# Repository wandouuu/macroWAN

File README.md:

# vWAN-micropad
PCB design for personal macropad!

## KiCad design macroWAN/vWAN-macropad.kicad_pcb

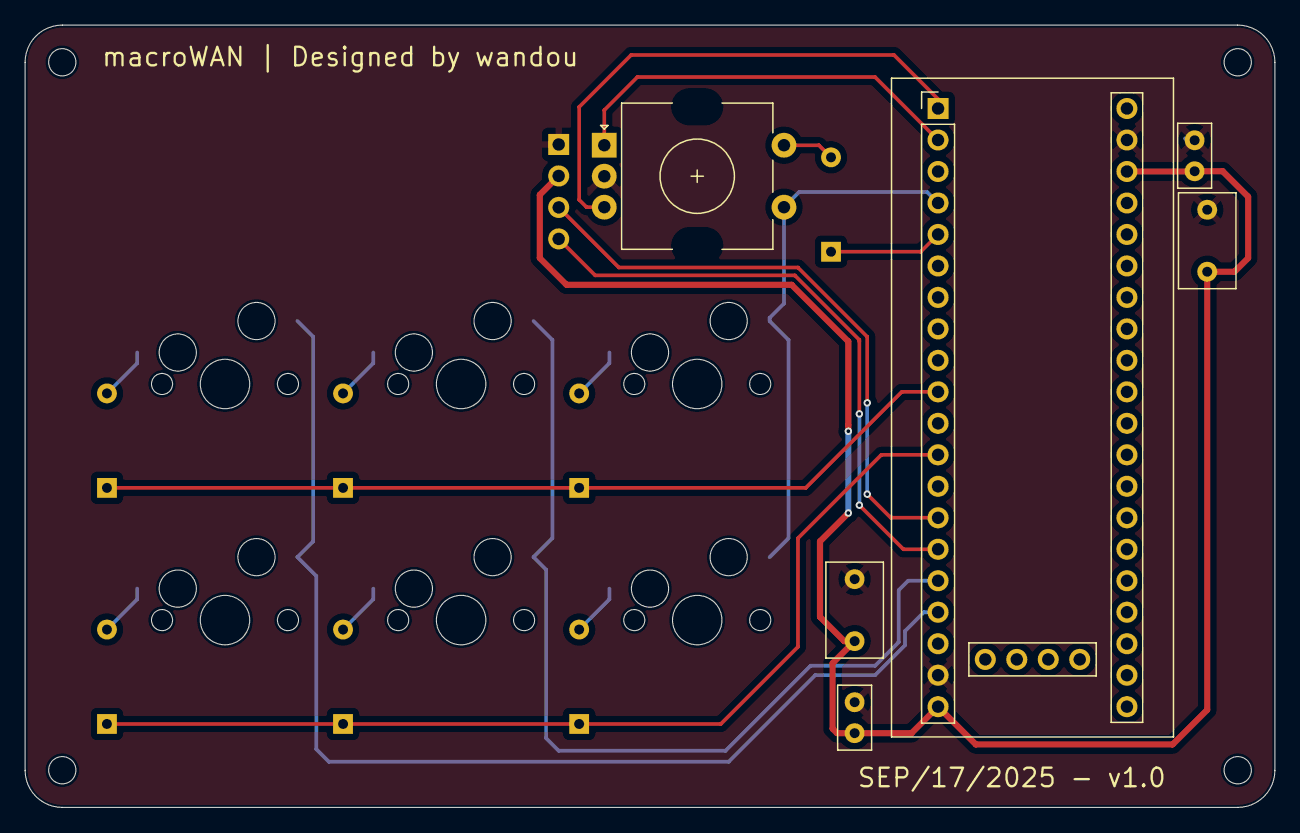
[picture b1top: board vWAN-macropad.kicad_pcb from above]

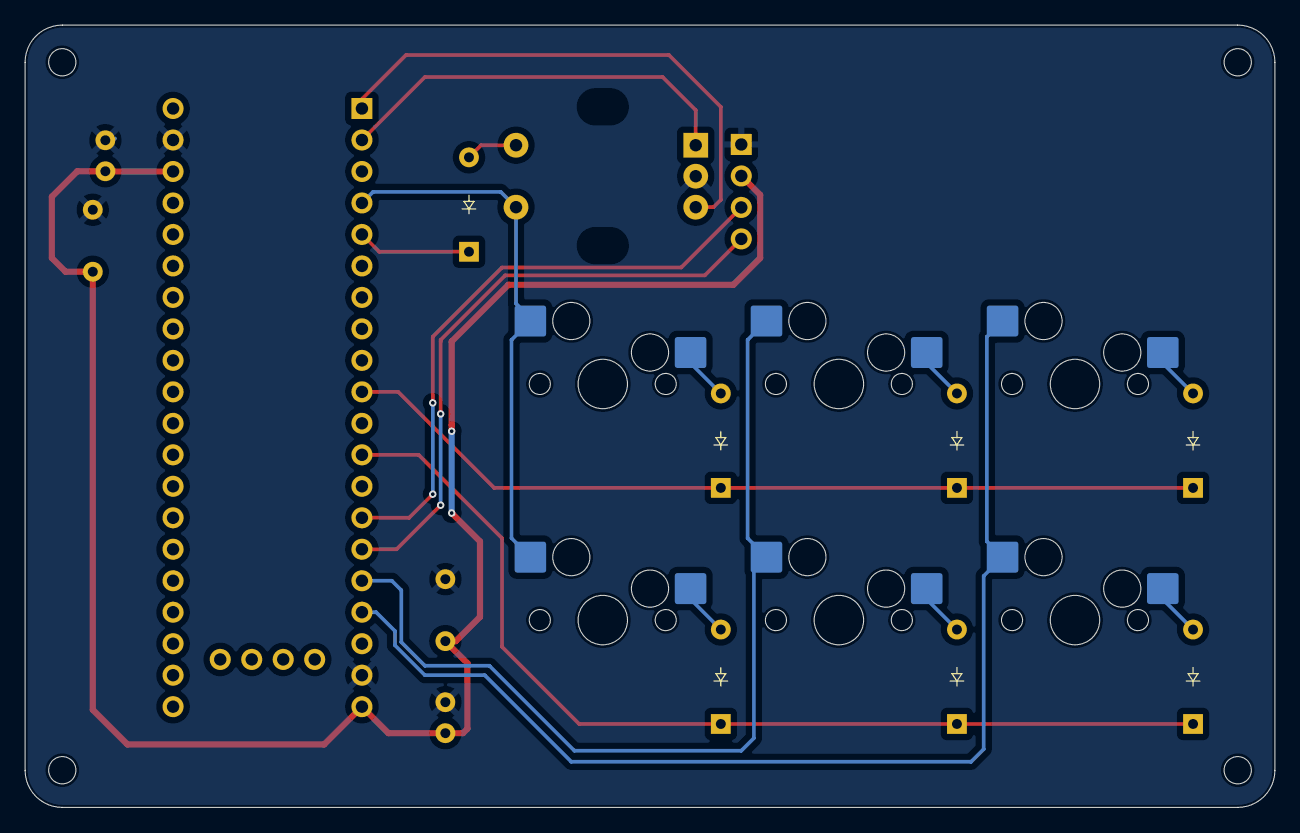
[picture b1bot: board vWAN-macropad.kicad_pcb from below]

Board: 2 copper layers, 100.8 x 63.1 mm, 24 parts (13 on the bottom side), 19 nets.

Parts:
C1, C2: 0.1uF; C_Disc_D5.0mm_W2.5mm_P2.50mm
C3, C4: 2.2uF; C_Disc_D7.5mm_W4.4mm_P5.00mm
D1, D2, D3, D4, D5, D6, D7: Diode; Diode_DO-35
H1, H2, H3, H4: MountingHole_Pad; MountingHole_2.2mm_M2_ISO7380
J1: OLED_128x32
SW1, SW2, SW3, SW4, SW5, SW6: Switch; MX-Hotswap-1U
SW7: RotaryEncoder_Switch; RotaryEncoder_EC11
U1: YAAJ_WeAct_BlackPill_Part_Like_SWD_Breakout; YAAJ_WeAct_BlackPill_SWD_2

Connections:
+3.3V: C1.2, C2.2, C3.2, C4.2, J1.2 (VCC), U1.20 (3V3), U1.38 (3V3)
Col 0: SW1.2, SW4.2, U1.17 (PB9)
Col 1: SW2.2, SW5.2, U1.16 (PB8)
Col 2: SW3.2, SW6.2, SW7.S1, U1.4 (PB15)
ENC_A: SW7.A, U1.2 (PB13)
ENC_B: SW7.B, U1.1 (PB12)
GND: C1.1, C2.1, C3.1, C4.1, J1.1 (GND), SW7.C, U1.19 (GND), U1.39 (GND)
unnamed: D1.2 (A), SW1.1
unnamed: D2.2 (A), SW2.1
unnamed: D3.2 (A), SW3.1
unnamed: D4.2 (A), SW4.1
unnamed: D5.2 (A), SW5.1
unnamed: D6.2 (A), SW6.1
unnamed: D7.2 (A), SW7.S2
Row 0: D7.1 (K), U1.5 (PA8)
Row 1: D1.1 (K), D2.1 (K), D3.1 (K), U1.10 (PA15)
Row 2: D4.1 (K), D5.1 (K), D6.1 (K), U1.12 (PB4)
SCL-SCK: J1.3 (SCL), U1.14 (PB6)
SDA: J1.4 (SDA), U1.15 (PB7)

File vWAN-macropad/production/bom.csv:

Designator,Footprint,Quantity,Value,LCSC Part #
"C1, C2",C_Disc_D5.0mm_W2.5mm_P2.50mm,2,0.1uF,
"D1, D2, D3, D4, D5, D6, D7",Diode_DO-35,7,Diode,
J1,OLED_128x32,1,OLED_128x32,
"SW1, SW2, SW3, SW4, SW5, SW6",MX-Hotswap-1U,6,Switch,
SW7,RotaryEncoder_EC11,1,RotaryEncoder_Switch,
U1,YAAJ_WeAct_BlackPill_SWD_2,1,YAAJ_WeAct_BlackPill_Part_Like_SWD_Breakout,

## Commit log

2025-07-10 Add schematic and PCB layout files
2025-07-10 Add submodules (libraries)
2025-07-10 Add submodules
2025-07-10 Add Blackpill v3.1 schematic
2025-07-17 Add submodules and edit schematics
2025-08-15 Update schematic + PCB files
2025-08-16 Update preliminary trace arrangement
2025-08-16 Edit project files
2025-08-18 Edit near final schematic + PCB
2025-08-18 Add misc files
2025-08-19 Add .gitignore
2025-08-19 Edit .gitignore
2025-09-18 Create LICENSE
2025-12-16 Add IOC configuration
2025-12-17 Defined ROW/COL pins
2025-12-17 Transferred into new file
2025-12-17 Add keypad initialization func
2025-12-19 Modify name + func declaration
2025-12-19 Add keymap and implemented scan logic
2025-12-20 Add USB handler files
2025-12-20 Add handler declarations
2025-12-24 Edit nInterfaceProtocol to keyboard
2025-12-30 Implement volume reading
2025-12-30 Finalize loop logic for HID volume
2026-01-01 Change void to uint8_t return type for send key
2026-01-01 Change name of send key func
2026-01-01 Refactor for loops
2026-01-01 Implement USB HID keyboard report (testing ready)
2026-01-02 Add SSD1306 lib
2026-01-02 Change location of keypad init func
2026-01-04 Add custom report descriptor and report OUT interrupt
2026-01-04 Implemented update volume func for SSD1306
2026-01-04 Corrected prev and curr volume variables
2026-01-04 Corrected prev + curr vol and flag
2026-01-07 Modify debouncing iter
2026-01-08 Add finalized loop for matrix, encoder, OLED
2026-01-08 Add finalized firmware
2026-01-08 Refactor gitmodules after renaming to macroWAN

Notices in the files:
macroWAN/vWAN-macropad.kicad_pcb:
microWAN © 2025 by Brendan Leung is licensed under CC BY-NC-SA 4.0
